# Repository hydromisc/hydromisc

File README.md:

# Hydromisc

This is a single PCBA with all the necessary I/O to automate a typical
small to mid-size hydroponic grow, controllable over Wi-Fi. It may also
be suitable for aquariums, ponds, or any other biological or chemical
process involving water treatment. Inputs and outputs include:

* 8x 12 V, 1 A outputs, intended for solenoid valves (but usable for other
actuators too)
* 6x 12 V, 0.5 A ouputs, intended for pumps, with current monitoring
* 4x 12 V, 0.25 A outputs, intended for peristaltic dosing pumps, with analog
voltage control
* 2x direct interfaces to a pH probe or other ion-selective electrode
* 2x direct interfaces to an EC (electrical conductivity) probe, reading around 1000 uS
* 2x direct interfaces to a resistive sensor (thermistor, photoresistor,
etc.), reading around 10k
* 2x digital interface to a temperature and humidity sensor
* 2x digital interface to a strain gauge (to measure weight or pressure)

Typical hydroponic practice is to maintain the solution at a target EC and
pH, using EC as a proxy for fertilizer concentration and dosing acid or
(rarely) alkali to adjust pH. I'm using this board now to control injector
pumps in a drain-to-waste system, open-loop with manual adjustment, and
also to maintain closed-loop EC and pH in a recirculating system.

## Firmware

The board is managed by an ESP32. Install the
[ESP-IDF](https://github.com/espressif/esp-idf) framework from Espressif,
and build and load the firmware from an ESP-IDF command prompt.

The board is a Wi-Fi client. The name and password for its access point
must be compiled in to the program, in Espressif's usual way, with `idf.py
menuconfig`. The board will automatically get an IP address over DHCP,
so you'll probably want to configure your router or other DHCP server to
assign a static IP based on the MAC address. The MAC address is unique
per board, since that's serialized in the ESP32 module.

The current firmware implements a simple interface to read the sensors
and write the actuators over http. I'm currently sequencing everything with
some shell scripts initiated by cron jobs on a Raspberry Pi, which invoke
curl to command this board. Any device and programming language capable of
making http requests could be used, though.

The outputs are described as "solenoid", "pump", and "dosing pump",
because that's the purpose for which I'm personally using them, and the
present interface is named around that model. They can of course be
used for other types of load too. The software interface is easily
extended if the present commands are inadequate or too confusingly-named.

    $ curl 'http://hydromisc/solenoid?k=3&t=20&'\
    'dosingA=90&dosingB=90&dosingPh=210&dosingAux=0'
    { "result": "solenoiding" }

Solenoid output k is energized for t seconds. For the same period,
the four dosing pumps are also energized, with the respective duty
cycles from 0 (off) to 254 (full on, ~12 VDC). The voltage applied to
the dosing pump is very roughly linear in duty cycle, but both that map
and the map from voltage to speed are quite inexact. If you're closing
the loop (e.g., dosing acid to achieve a particular pH), then this may
not matter, since your control loop will automatically correct that. If
accuracy is important, then the pump should be calibrated, for example
by measuring the amount of liquid dispensed using a graduated cylinder
or weighing scale.

The solenoid output is powered for three seconds after the pumps stop.
This is to avoid closing the solenoid valves with pressure in the system,
since the pumps will continue to operate briefly after losing power. If
the dosing pumps feed directly into a single reservoir, then this and
everything else about the solenoids may be ignored.

    $ curl 'http://hydromisc/pump?k=4&t=15'
    { "result": "pumping" }

Pump output k is energized for t seconds. The measured current (up to about
500 mA) is recorded.

    $ curl 'http://hydromisc/current'
    { "result": "current","current": [ 71, 65, 74, 69, 78, 74, 80, 73, 63,
    73, 65, 68, 74, 64, 60 ] }

The current from the most recent /pump is reported, in units of milliamps
at one sample per second. If this hasn't yet completed, a full-length
trace is reported but future samples are 0.

    $ curl 'http://hydromisc/stop'
    { "result": "stopping" }

All (solenoid, pump, dosing pump) outputs are de-energized immediately.

    $ curl 'http://hydromisc/sensors'
    { "result": "sensors", "ec0": 984, "ec1": 47, "ph0": 41, "ph1": -320,
    "dcr0": 210000, "dcr1": 210000, "temp0": 25.7, "humidity0": 54.0,
    "temp1": -9999.9, "humidity1": -9999.9, "sg0": 0, "sg1": -1 }

All sensors are measured and reported.

The pH electrode voltage is returned in millivolts, and your software
must convert to pH. To a first order, the map from voltage to pH is
linear, with zero volts corresponding to pH = 7.0, and a slope around
59 mV/unit around room temperature (which may be calculated using the
Nernst equation).

You should calibrate by measuring the voltage in two solutions of known
pH (e.g., 4.0 and 6.9), and interpolating linearly between the two. For
example:

    const V69 = 8;      // millivolts in pH 6.9 calibration buffer
    const V40 = -152;   // millivolts in pH 4.0 calibration buffer

    const slope = (V69 - V40)/(6.9 - 4.0);

    let ph = 6.9 + (resp.ph0 - V69)/slope;

Your software must also correct for temperature if desired; though in
typical hydroponic applications, the pH is close enough to neutral that
it doesn't matter too much. To a first order, the slope changes with
temperature but the offset does not, so the tempco is very small when the
output voltage is small.

Other ion-selective electrodes (e.g., for nitrate, potassium, etc.) should
also work with this interface circuit. Consult the electrode documentation
for the calibration procedure, which should be specified in terms of
millivolts from the meter. The reference electrode would need to go to
the BNC shell (Vref ~ 1.2 V), not ground.

EC is returned directly in microsiemens, uS. For example, a resistance
of 1kohm is equal to 1000 uS. Your software must convert based on the
cell dimensions (to convert from uS to uS/cm; a cell constant of 1 cm
is typical so that may be trivial), and also perform any temperature
compensation if desired. If you already have a different EC meter,
then you can use that with a sample of hydroponic solution to transfer
calibration. If not, then you can calibrate in a solution of 1000 mg/L
sodium chloride (table salt), which has conductivity of 2000 uS/cm at
25 degrees Celsius.

In concept, any two wires the right length and distance apart (e.g.,
on the order of 1 cm) could be immersed in solution, and could serve
as your EC electrode. You may prefer to buy a purpose-built electrode,
though. That may have a plastic sheath that protects the electrodes
from mechanical damage with a slit to avoid trapping air bubbles. The
electrode material should also have good electrochemical properties.
Inexpensive electrodes will generally use stainless steel. The most
expensive electrodes will use a thin coating of platinum black, which
reduces error by reducing the series resistance due to electrode
polarization. Either is likely fine in practice.

Electrodes may also be inserted into media, in which case they measure
a product of the solution EC and the media water content. An EC channel
can also be used as a binary liquid level sensor, by placing the
electrodes just below the threshold level. In such use, take care that
the electrodes are far enough apart that surface tension can't hold
a drop of solution even when they aren't immersed.

To measure water (or other) temperature, you can use a thermistor. Some
EC or pH probes will have a thermistor integrated in the probe,
or you can buy one separately. The resistance of that thermistor
(or any other resistive sensor) is returned directly in ohms. Your
software must convert to temperature. For a typical NTC thermistor,
the logarithm of the resistance is proportional to the reciprocal of
absolute temperature. For example:

    // we calibrated at 22 degrees Celsius, and measured 10435 ohms
    const calLogR = Math.log(10435);
    const calTemp = 22;

    // from some random NTC thermistor datasheet, or you could also do a
    // two-point calibration
    const slope = 0.0002578;

    let Tinv = 1/(273 + calTemp) + slope*(Math.log(resp.dcr0) - calLogR);
    let T = 1/Tinv - 273;

I'm also using that interface with a photoresistor to count hours of sun,
though I'm doing a simple binary threshold (to distinguish direct sun
vs. shade) and not a full continuous calibration.

To measure air temperature and humidity, connect an AM2301 on either 2x3
position connector to ground (black), +3V3 (red), and DIG_xOUT (yellow).
Temperature is returned in degrees Celsius, and humidity in percent RH.
A pull-up resistor from red to yellow may be required if the wires are long,
since we otherwise just get the ESP32's on-chip pull-up.

To measure a strain gauge, connect an HX710 to ground, +3V3, DIG_xCK
(SCK), and DIG_xIN (DOUT). The result is returned in raw ADC units,
which you can calibrate to force or pressure with a linear offset and
scale. I use this to measure liquid level with a "bubbler" system,
measuring the hydrostatic pressure in an air-filled tube at the bottom
of the tank. (It's necessary to bubble a slow trickle of air through the
tube, or else tiny leaks will cause it to eventually fill with water; but
since I'm already aerating my tanks, that just takes a tee and a needle
valve. Such systems are common in process industries, crude but cheap
and reliable. My system is okay but not great, since the pressure sensor
has a large tempco. I used an additional AM2301 very close to the sensor
to compensate, but there's still an inch or so worth of residual error.)

You can simultaneously connect an HX710 and an AM2301 to the same
2x3 connector, since they use different data pins.

    $ curl 'http://hydromisc/conf?dosingAPhase=63&dosingBPhase=4032&'\
    'dosingPhPhase=4095&dosingAuxPhase=4095&runBigPump=1'
    { "result": "configured" }

By default, the dosing pumps run continuously during a /solenoid call.
Here they can also be configured to run intermittently, in 100 ms
intervals on a 12-interval (1.2 s) period. The operation of each dosing
pump may be specified here as a bitmap, 12 bits as a decimal number. For
example, the decimal number 63 is equal to 12'b000000111111, so dosing
pump A is on with duty cycle 1/2, 600 ms on followed by 600 ms off. The
decimal number 4032 is equal to 12'b111111000000, so dosing pump B is
also on with duty cycle 1/2 but with opposite phase.

When peristaltic pumps are used as fertilizer injectors, this intermittent
operation can achieve lower injection rates than can be reliably achieved
with low pump voltage (since the transfer characteristic from voltage to
flow varies a lot at low voltage). The phase may be chosen to minimize
risk of mixing before dilution.

By default, the output BIG_PUMP is energized during a /solenoid call. This
may be disabled by setting runBigPump=0.

## Getting Hardware

For the moment, this hardware isn't commercially available in assembled
form. (That may change, since this is open hardware that anyone can build
and sell; I'll add links if and when it does.) You'll therefore have to
buy the bare PCB and parts kit, and assemble yourself. This PCBA has no
leadless or fine-pitch components, so it can be hand-assembled with a
soldering iron and moderate skill.

Note that rev A of the PCB has one major erratum, a missing pull-up on
ESP32_EN, plus some smaller issues that degrade analog performance. I've
corrected these in rev C, which is the head revision in git, but never
actually built and tested that. So it's possible there's still a mistake,
though the risk should be small. Full details of the changes are in
[board/README.md](https://github.com/hydromisc/hydromisc/blob/master/board/README.md).

Total cost to build one board is around:

Item | Cost
----------- | --------------
bare PCB, PCBWay | $30
components, Digi-Key | $60

All connectors are Molex Mini-Fit Jr., a very popular series. It's
possible to solder the cable-end connectors rather than crimping
them, but not recommended. The official crimp tool is expensive. I've used
a third-party "SN-28B", which isn't actually designed for that family
but is cheap and barely adequate, if I crimp first with the largest
die and then again with the middle one.

To program the board, use any USB-to-serial adapter with +3V3 logic levels,
for example an FT232R. Take care that you need access to RTS, which some
such boards and cables don't break out. On CN15, connect:

* ground to ground
* +3V3 to nothing
* USBSER_RX to ESP32_TXD0
* USBSER_TX to ESP32_RXD0
* USBSER_DTR to ESP32_IO0
* USBSER_RTS to ESP32_EN

Program with `idf.py flash` in the usual way. Disconnect digital expansion
devices when programming, since they can interfere.

For complete automated control of EC and pH, you might add:

Item | Cost
----------- | --------------
pH electrode, Yieryi | $15
EC electrode | $15
3x aquarium-type dosing pump | $30
water fill solenoid valve | $15

See my brief
[review of the sensors and actuators now cheaply available on Chinese markets](https://github.com/hydromisc/hydromisc/blob/master/doc/sensors-actuators.md).

Then you might periodically (e.g., minutes to hours) measure EC and pH
with /sensors. You could also monitor solution level, using another EC
electrode positioned high in the tank or using a float switch. The board
has no binary digital inputs, but the DC resistance or EC channels work
with switch contacts too. Then using /solenoid, you could add water,
fertilizer, and acid as required to maintain desired liquid level,
EC and pH.

You would typically aim to keep pH constant, for example with simple
hysteretic (bang-bang) control--add phosphoric if the pH is too high,
or add potassium carbonate if the pH is too low, with a significant
deadband (e.g., 0.5 units) so the acid and alkali don't fight it out
and leave too much potassium phosphate in the solution. In most cases
the alkali would actually be unnecessary, since the natural alkalinity
of the water supplies all necessary pH rise. That's the reason why only
one dosing pump channel is labeled "pH", though the AUX channel could
be used for alkali if desired.

Control of EC is more complicated, since unwanted ions (e.g., sodium
and chloride) will accumulate over time in the solution. So constant EC
probably means rising unwanted ions but falling NPK, and will eventually
result in deficiency. If you maintain constant EC, then you'll need to
change the reservoir often. You can waste less water by allowing slow
rise, though managing that without detailed water analyses is somewhat
uncertain. In all cases, fertilizer should be dosed in a way that doesn't
risk mixing of Part A and Part B before they're fully diluted, to avoid
precipitation (nutrient lockout) from the reaction between calcium ions
and phosphate or sulfate. For example, dose at opposite ends of the tank,
or allow sufficient time to mix between parts.

Of course more complicated automation is possible too. For example, this
board could manage multiple reservoirs simultaneously, or sense EC and
pH both in the reservoir and in returning solution from NFT channels, or
manage fertilizer injectors for a drain-to-waste system. The large number
of inputs and outputs is intended to provide flexibility to interface to
almost any conceivable system's sensors and actuators, with the automated
behavior determined by the software that commands this board.

## Circuit Explanation

Input power is +12 V, which feeds the power outputs directly. It also
feeds a buck converter that makes our +5V, and a buck converter that
makes Vuser, arbitrarily adjustable with a trimpot. An LDO makes +3V3
from +5V, and all our logic runs from that.

The ESP32 is a module with integrated antenna. It would be better for
the antenna tuning if the board outline had a cutout for that, but I
preferred mechanical robustness over antenna range. The ESP32 drives
two 8-bit serial-input, parallel-output shift registers, which function
as GPIO expanders and gate drivers for the pump and solenoid power
FETs. Max current for the solenoid outputs is determined by thermals due
to I^2\*Rdson. I haven't measured that temperature rise, but something
around an amp should be quite safe. Max current for the pump outputs is
determinated by the 2.2 ohm low-side current-sense resistor, and could
be increased by decreasing that.

The dosing pump gates are driven directly by ESP32 PWM outputs. A
series LC makes the negative-ground equivalent of a buck converter
on those outputs, enabling us to drive the dosing pumps not with PWM
but with a programmable DC voltage. This decreases radiated emissions,
and provides something like a constant voltage output as long as the
converter remains in continuous conduction.

The pump outputs return their ground current through a current-sense
resistor, and an ESP32 ADC channel measures the voltage across that. This
enables us to measure pump current. For example, if pump current
is much higher when pumping water than when pumping air, this lets us
measure the volume of water pumped out of a tray by measuring when the
pump current drops. The current can also be used for health monitoring, to
confirm the pump is actually connected and operating with expected load.

A pH electrode develops a voltage around 0 V at pH 7, plus or minus
roughly 59 mV per pH unit at room temperature. Its output impedance may be
many megohms, so we measure that voltage with an electrometer-type opamp,
with femtoamp input current. To mitigate leakage resistance across our
PCB (e.g., due to ionic contamination from flux residue), we surround
the sensitive trace with a driven shield held at the same voltage as that
sensitive node. I've seen no trouble due to leakage even without cleaning
flux, though I live in a dry climate and it would be better to clean that.

Since the pH electrode voltage may be positive or negative and we don't
have a negative supply, we connect its "ground" to a 1.2 V reference. This
means that any electrical connection between our circuit ground and
the solution being measured will result in an incorrect measurement,
though the shunt regulator that generates that rail can survive a short
to ground without damage. The shield of the BNC connectors is 1.2 V,
not ground. As long as the board is powered from an isolated power supply
(for example, a typical mains-operated power brick), no further attention
should be required; but take care not to de-isolate it, for example by
attaching board ground to any metal that touches the solution.

Even with DC isolation, a significant 60 Hz (or 50 Hz) component may
be present on the pH probe voltage. If this saturates the front-end
amplifier, then no subsequent low-pass could recover the correct DC
voltage. We address this with a capacitor across the pH probe. The
resulting low-pass time constant is poorly-controlled, since it's a
function of the probe output resistance.  That's fine in practice though,
since pH shouldn't change significantly over any timescale faster than
minutes.

We pull both sides of the EC electrode up to +3V3 through 1k
resistors, so they both rest at +3V3 with respect to circuit ground, 0 V
differential. To measure EC, we pull one side to ground through an n-FET,
and then measure the voltage of the other, making a voltage divider
between the known 1k and the unknown resistance under test. We then
repeat the process for the other side, restoring zero DC voltage across
the electrode to avoid polarization. The EC electrode is also AC-coupled
through 22 uF ceramic capacitors, guaranteeing zero DC voltage even if
the software misbehaves or the resistors don't perfectly match and, more
importantly, presenting high imepedance at DC so the EC electrode doesn't
short out a pH electrode immersed in the same sample cup. Assuming EC
around 2 mS/cm and cell constant around 1 cm, we get a high-pass time
constant around 4 ms, which is much slower than our measurement period
of ~500 us. Electrolytic capacitors can't be used for that AC-coupling,
since the leakage current is too high.

A similar approach may be used to measure EC with almost
any microcontroller and no additional components beyond the
reference resistors and AC-coupling capacitors, by configuring that
microcontroller's I/O pin as an output low to ground it. I chose to use
the external FETs here because I'd run out of microcontroller pins, and
because the lower and more consistent Rdson improves accuracy at high EC
(since that appears in series with the resistance under test).

## Information Security

None whatsoever. Use this only behind a firewall (like a typical
residential NAT router), on a network with trusted users only. If you
need remote access, expose it through a properly-secured jump box or VPN,
not directly.

## Warranty and Life Safety

THERE IS NO WARRANTY FOR THIS SOFTWARE OR HARDWARE, TO THE EXTENT
PERMITTED BY APPLICABLE LAW. WE PROVIDE THE SOFTWARE OR HARDWARE "AS IS"
WITHOUT WARRANTY OF ANY KIND, EITHER EXPRESSED OR IMPLIED, INCLUDING,
BUT NOT LIMITED TO, THE IMPLIED WARRANTIES OF MERCHANTABILITY AND FITNESS
FOR A PARTICULAR PURPOSE.

DO NOT USE THIS SOFTWARE OR HARDWARE IN SITUATIONS WHERE ITS FAILURE COULD
RESULT IN DANGER TO HUMAN LIFE. For example, don't dose concentrated acid
and rely on correct operation of this board to safely dilute it--instead
dose a higher volume of less concentrated acid, or use safer chemistry
(monopotassium phosphate, etc.). Also think carefully about the risk of
overflowing water, dead plants or fish, and other damage, and don't rely
on software to prevent it.

## License

The firmware is licensed under the GPLv3 or later. The legal framework
for open hardware is poorly-established, but you may build and sell, give
away, or otherwise transfer any number of hydromisc boards, provided that:

* any software loaded on the board is free software (as defined by
any OSI-approved license), and that software is not intended primarily
as a bootloader or other tool to load, program, or otherwise enable use
of non-free software; and

* you do not falsely claim ownership of the design, or any affiliation
with this project beyond your permission to build boards per above.

## Next steps

For now, this project is useful only to people with sufficient programming
skill to build and load the firmware, and to use the http interface
above. For future, it would be nice to:

* Integrate with existing control software (Mycodo, home automation packages,
etc.)

* And/or, add logic on the ESP32 itself for timed irrigations and
closed-loop dosing based on measured pH and EC, to allow this board
to work standalone with no need for the network except for initial
configuration. Firmware to log and graph (as a web page) sensors over
time would also be helpful in standalone use.

* Add a friendly mode to configure Wi-Fi settings, since those currently
must be compiled in. For example, if some combination of pins is jumpered
at startup, appear as a Wi-Fi access point to which the user can connect
and provide the real access point name and password. Then save those
credentials in flash, and use them after reset.

* Clean up how concurrency is managed in the firmware. The present code
seems to work, but it's a lazy hack that's hard to analyze for races.

I might eventually do some of that work myself, but I have limited time
and welcome other contributors. Please feel free to use GitHub issues to
discuss potential new features or anything else.

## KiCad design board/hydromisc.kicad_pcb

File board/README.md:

There are three revisions of the PCB:

* rev A - I built this, and it works except that I forgot the pull-up on
ESP32_EN. Solder a 10k resistor from ESP32_EN to +3V3 (for example, near
CN15), or else the ESP32 module won't start when the programmer is
disconnected.

* rev B - This adds the missing pull-up, as R54. It also adds R55 and
R56 from Vuser to ground, enabling use of LM2596 parts from vendors
(e.g. ON Semi) that have much higher leakage current than the National/TI
original, up to 2 mA! A lightly-loaded Vuser may lose regulation when
Ileakage\*Rpulldown > Vsetpoint, and that R was previously just the
feedback divider.

* rev C - This adds capacitors to create a passive low-pass on the pH
inputs, improving 60 Hz (or 50 Hz) rejection and thus reducing noise
e.g. when the probe is connected with long wires. It also changes the
series resistors between Vref and the BNC shield from 1k to zero-ohm,
since the shunt regulator that makes Vref can survive a short-circuit
to ground with no problem and that resistance worsens noise performance.

The head revision in git is rev C; but I've never actually built this
revision, so it's possible there's still a mistake. That risk should be
very small, though. I'll amend this note if/when someone builds rev C
and reports back.

This is a two-layer board, designed to PCBWay's standard design rules.
Almost any vendor should be able to make this, though. 1.6mm thick,
1 oz/ft^2 copper.

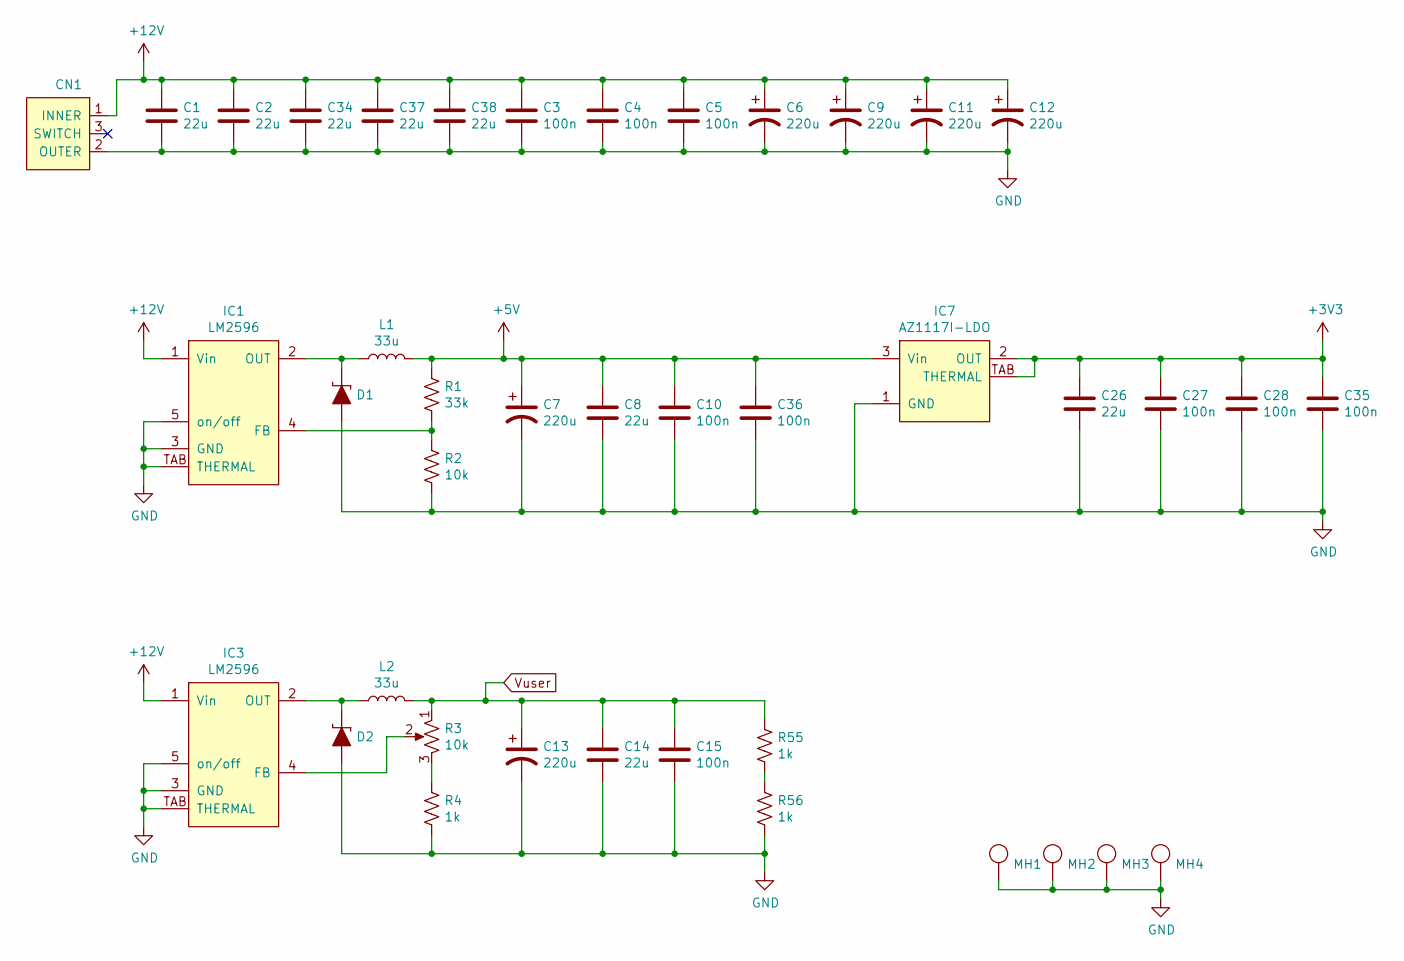
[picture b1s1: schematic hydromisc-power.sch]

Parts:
C1, C2, C8, C14, C26, C34, C37, C38: 22u; HM_1206
C3, C4, C5, C10, C15, C27, C28, C35, C36: 100n; HM_0603
C6, C7, C9, C11, C12, C13: 220u; HM_C_8MM_3.5MM
CN1: DC_COAX_POWER_NO_SHIELD; HM_DC_COAX_POWER_PJ-102AH
D1, D2: diode-schottky; HM_DIODE_SMB
IC1, IC3: LM2596; HM_TO-263-5
IC7: AZ1117I-LDO; HM_SOT-223
L1, L2: 33u; HM_L_SUMIDA_104CDMCCDS
MH1, MH2, MH3, MH4: MOUNTING_HOLE; HM_MOUNTING_HOLE_6MM_3MM
R1: 33k; HM_0603
R2: 10k; HM_0603
R3: 10k; HM_TRIMPOT_AB_HA06
R4, R55, R56: 1k; HM_0603

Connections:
+3V3: C26.1, C27.1, C28.1, C35.1, IC7.2 (OUT), IC7.TAB (THERMAL); also elsewhere on the board
+5V: C7.1, C8.1, C10.1, C36.1, IC7.3 (Vin), L1.2, R1.1; also elsewhere on the board
+12V: C1.1, C2.1, C3.1, C4.1, C5.1, C6.1, C9.1, C11.1, C12.1, C34.1, C37.1, C38.1, CN1.1 (INNER), IC1.1 (Vin), IC3.1 (Vin); also elsewhere on the board
GND: C1.2, C2.2, C3.2, C4.2, C5.2, C6.2, C7.2, C8.2, C9.2, C10.2, C11.2, C12.2, C13.2, C14.2, C15.2, C26.2, C27.2, C28.2, C34.2, C35.2, C36.2, C37.2, C38.2, CN1.2 (OUTER), D1.A, D2.A, IC1.3 (GND), IC1.5 (on/off), IC1.TAB (THERMAL), IC3.3 (GND), IC3.5 (on/off), IC3.TAB (THERMAL), IC7.1 (GND), MH1.1, MH2.1, MH3.1, MH4.1, R2.2, R4.2, R56.2; also elsewhere on the board
unnamed: D1.K, IC1.2 (OUT), L1.1
unnamed: D2.K, IC3.2 (OUT), L2.1
unnamed: IC1.4 (FB), R1.2, R2.1
unnamed: IC3.4 (FB), R3.2
unnamed: R3.3, R4.1
unnamed: R55.2, R56.1
Vuser: C13.1, C14.1, C15.1, L2.2, R3.1, R55.1; also elsewhere on the board

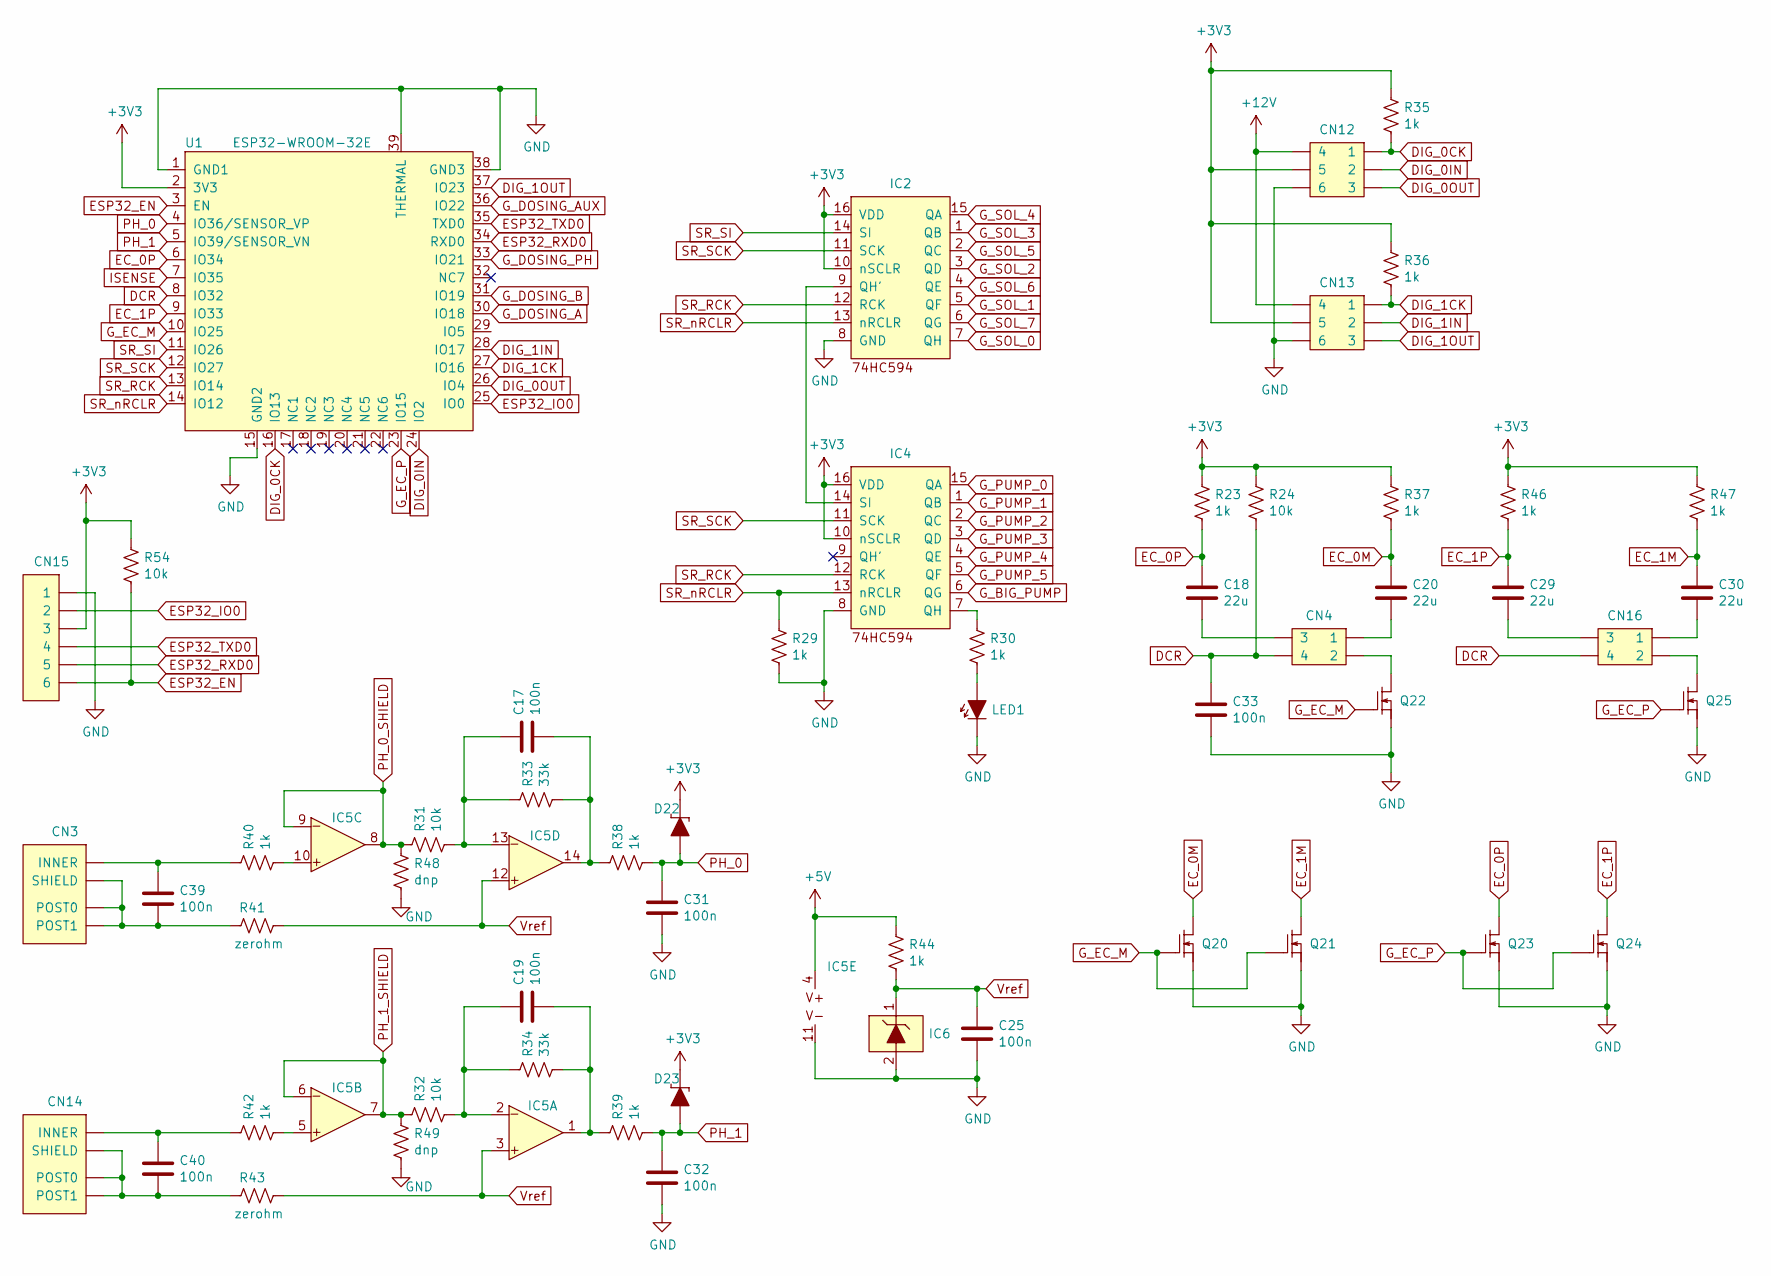
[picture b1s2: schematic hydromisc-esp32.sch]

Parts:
C17, C19, C25, C31, C32, C33, C39, C40: 100n; HM_0603
C18, C20, C29, C30: 22u; HM_1206
CN3, CN14: COAX_CONNECTOR; HM_BNC_MOLEX_TH_RA
CN4, CN16: MOLEX_2x2; HM_MOLEX_172448_2x2
CN12, CN13: MOLEX_2x3; HM_MOLEX_172448_2x3
CN15: HEADER_6; HM_HEADER_6_0.100_INCH
D22, D23: diode-schottky; HM_SOD-123
IC2, IC4: 74HC594; HM_SOIC-16
IC5: opamp; HM_SOIC-14
IC6: vref-diode; HM_SOT-23_123
LED1: diode-led; HM_LED_CUBE_3MM
Q20, Q21, Q22, Q23, Q24, Q25: NFET; HM_SOT-23_123
R23, R29, R30, R35, R36, R37, R38, R39, R40, R42, R44, R46, R47: 1k; HM_0603
R24, R31, R32, R54: 10k; HM_0603
R33, R34: 33k; HM_0603
R41, R43: zerohm; HM_0603
R48, R49: dnp; HM_0603
U1: ESP32-WROOM-32E; HM_ESP32-WROOM-32E

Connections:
+3V3: CN12.5, CN13.5, CN15.3, D22.K, D23.K, IC2.10 (nSCLR), IC2.16 (VDD), IC4.10 (nSCLR), IC4.16 (VDD), R23.1, R24.1, R35.2, R36.2, R37.1, R46.1, R47.1, R54.1, U1.2 (3V3); also elsewhere on the board
+5V: IC5.4 (V+), R44.1; also elsewhere on the board
+12V: CN12.4, CN13.4; also elsewhere on the board
DCR: C33.1, CN4.4, CN16.4, R24.2, U1.8 (IO32)
DIG_0CK: CN12.1, R35.1, U1.16 (IO13)
DIG_0IN: CN12.2, U1.24 (IO2)
DIG_0OUT: CN12.3, U1.26 (IO4)
DIG_1CK: CN13.1, R36.1, U1.27 (IO16)
DIG_1IN: CN13.2, U1.28 (IO17)
DIG_1OUT: CN13.3, U1.37 (IO23)
EC_0M: C20.1, Q20.3 (D), R37.2
EC_0P: C18.1, Q23.3 (D), R23.2, U1.6 (IO34)
EC_1M: C30.1, Q21.3 (D), R47.2
EC_1P: C29.1, Q24.3 (D), R46.2, U1.9 (IO33)
ESP32_EN: CN15.6, R54.2, U1.3 (EN)
ESP32_IO0: CN15.2, U1.25 (IO0)
ESP32_RXD0: CN15.5, U1.34 (RXD0)
ESP32_TXD0: CN15.4, U1.35 (TXD0)
GND: C25.2, C31.2, C32.2, C33.2, CN12.6, CN13.6, CN15.1, IC2.8 (GND), IC4.8 (GND), IC5.11 (V-), IC6.2 (-), LED1.K, Q20.2 (S), Q21.2 (S), Q22.2 (S), Q23.2 (S), Q24.2 (S), Q25.2 (S), R29.2, R48.2, R49.2, U1.1 (GND1), U1.15 (GND2), U1.38 (GND3), U1.39 (THERMAL); also elsewhere on the board
G_BIG_PUMP: IC4.6 (QG); also elsewhere on the board
G_DOSING_A: U1.30 (IO18); also elsewhere on the board
G_DOSING_AUX: U1.36 (IO22); also elsewhere on the board
G_DOSING_B: U1.31 (IO19); also elsewhere on the board
G_DOSING_PH: U1.33 (IO21); also elsewhere on the board
G_EC_M: Q20.1 (G), Q21.1 (G), Q22.1 (G), U1.10 (IO25)
G_EC_P: Q23.1 (G), Q24.1 (G), Q25.1 (G), U1.23 (IO15)
G_PUMP_0: IC4.15 (QA); also elsewhere on the board
G_PUMP_1: IC4.1 (QB); also elsewhere on the board
G_PUMP_2: IC4.2 (QC); also elsewhere on the board
G_PUMP_3: IC4.3 (QD); also elsewhere on the board
G_PUMP_4: IC4.4 (QE); also elsewhere on the board
G_PUMP_5: IC4.5 (QF); also elsewhere on the board
G_SOL_0: IC2.7 (QH); also elsewhere on the board
G_SOL_1: IC2.5 (QF); also elsewhere on the board
G_SOL_2: IC2.3 (QD); also elsewhere on the board
G_SOL_3: IC2.1 (QB); also elsewhere on the board
G_SOL_4: IC2.15 (QA); also elsewhere on the board
G_SOL_5: IC2.2 (QC); also elsewhere on the board
G_SOL_6: IC2.4 (QE); also elsewhere on the board
G_SOL_7: IC2.6 (QG); also elsewhere on the board
ISENSE: U1.7 (IO35); also elsewhere on the board
unnamed: C17.1, IC5.13 (D-), R31.2, R33.1
unnamed: C17.2, IC5.14 (DOUT), R33.2, R38.1
unnamed: C18.2, CN4.3
unnamed: C19.1, IC5.2 (A-), R32.2, R34.1
unnamed: C19.2, IC5.1 (AOUT), R34.2, R39.1
unnamed: C20.2, CN4.1
unnamed: C29.2, CN16.3
unnamed: C30.2, CN16.1
unnamed: C39.1, CN3.INNER, R40.1
unnamed: C39.2, CN3.POST0, CN3.POST1, CN3.SHIELD, R41.1
unnamed: C40.1, CN14.INNER, R42.1
unnamed: C40.2, CN14.POST0, CN14.POST1, CN14.SHIELD, R43.1
unnamed: CN4.2, Q22.3 (D)
unnamed: CN16.2, Q25.3 (D)
unnamed: IC2.9 (QH'), IC4.14 (SI)
unnamed: IC4.7 (QH), R30.1
unnamed: IC5.5 (B+), R42.2
unnamed: IC5.10 (C+), R40.2
unnamed: LED1.A, R30.2
PH_0: C31.1, D22.A, R38.2, U1.4 (IO36/SENSOR_VP)
PH_0_SHIELD: IC5.8 (COUT), IC5.9 (C-), R31.1, R48.1
PH_1: C32.1, D23.A, R39.2, U1.5 (IO39/SENSOR_VN)
PH_1_SHIELD: IC5.6 (B-), IC5.7 (BOUT), R32.1, R49.1
SR_RCK: IC2.12 (RCK), IC4.12 (RCK), U1.13 (IO14)
SR_SCK: IC2.11 (SCK), IC4.11 (SCK), U1.12 (IO27)
SR_SI: IC2.14 (SI), U1.11 (IO26)
SR_nRCLR: IC2.13 (nRCLR), IC4.13 (nRCLR), R29.1, U1.14 (IO12)
Vref: C25.1, IC5.3 (A+), IC5.12 (D+), IC6.1 (+), R41.2, R43.2, R44.2

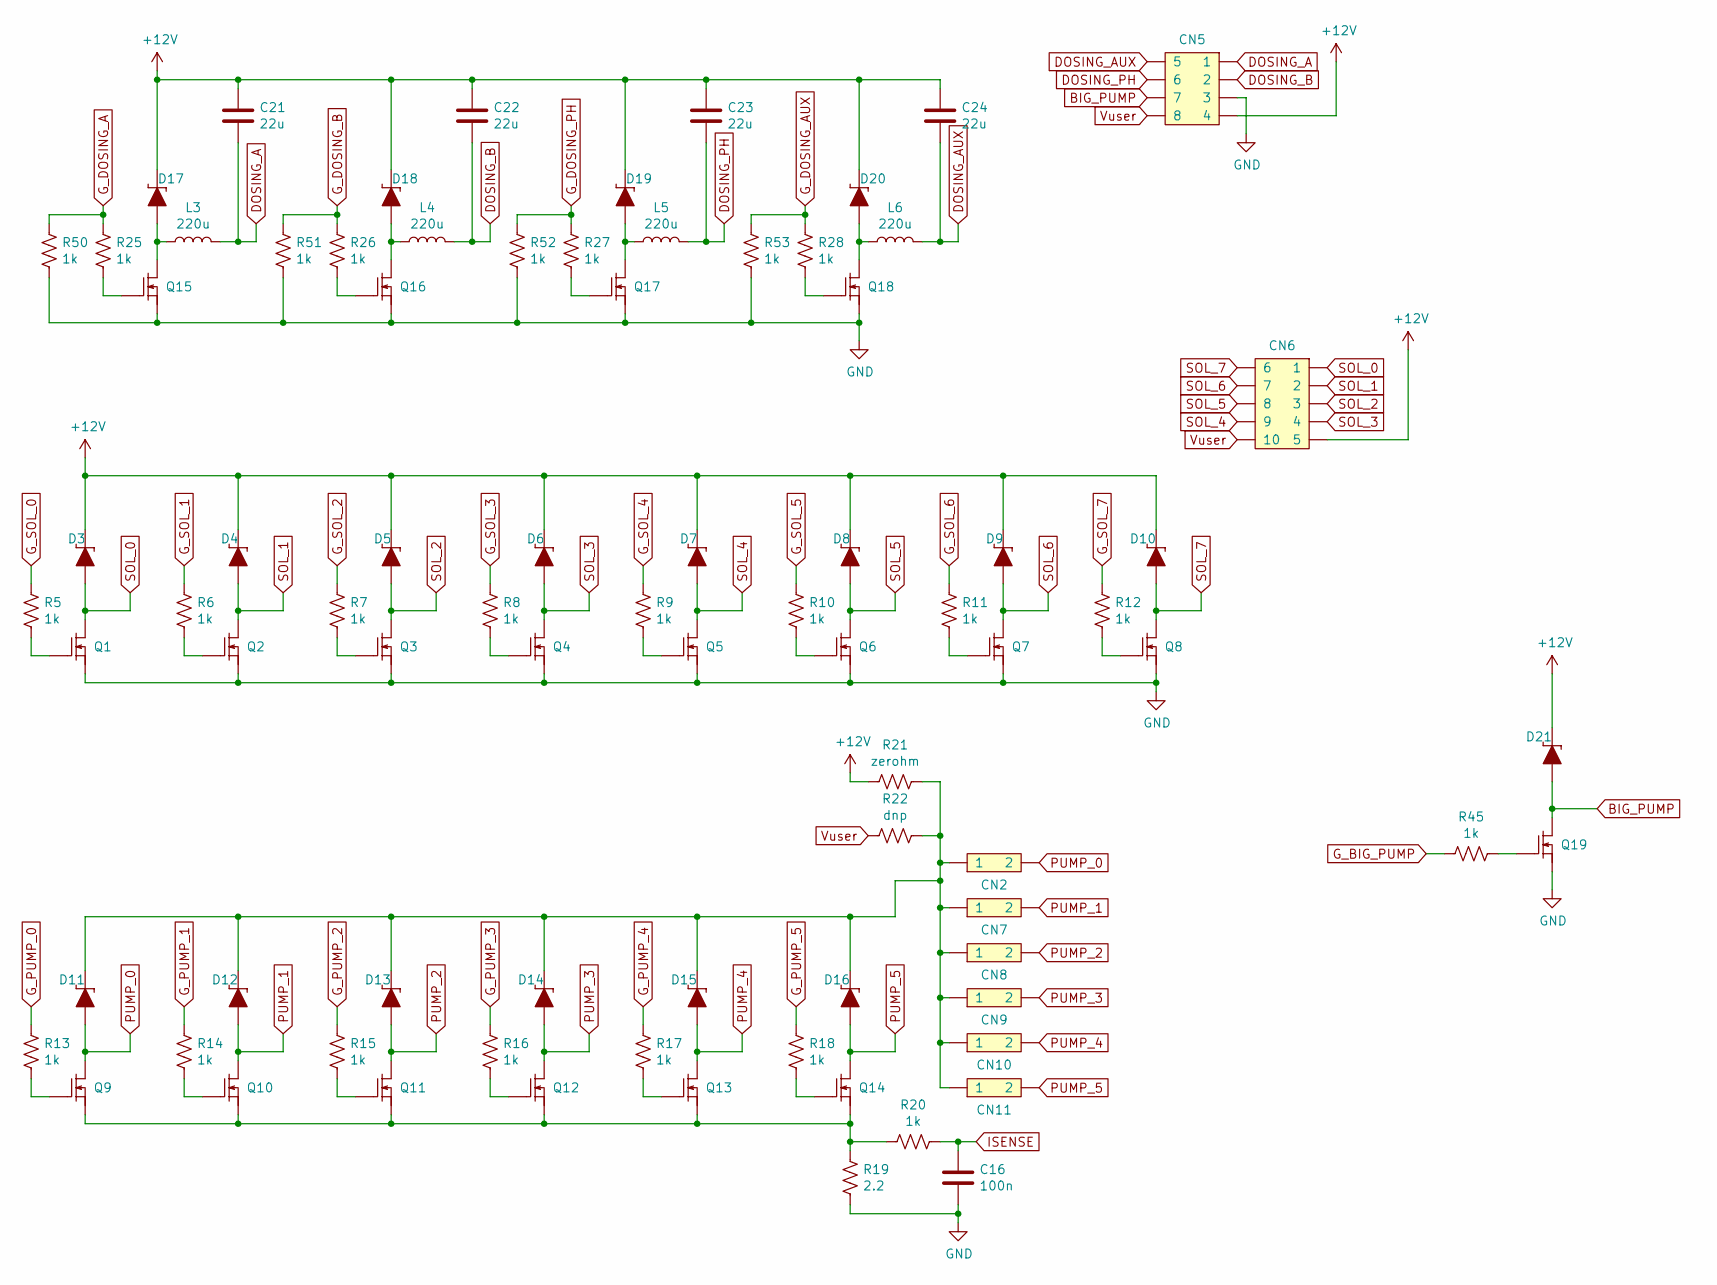
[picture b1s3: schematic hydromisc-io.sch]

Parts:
C16: 100n; HM_0603
C21, C22, C23, C24: 22u; HM_1206
CN2, CN7, CN8, CN9, CN10, CN11: MOLEX_2x1; HM_MOLEX_172448_2x1
CN5: MOLEX_2x4; HM_MOLEX_172448_2x4
CN6: MOLEX_2x5; HM_MOLEX_172448_2x5
D3, D4, D5, D6, D7, D8, D9, D10, D11, D12, D13, D14, D15, D16, D17, D18, D19, D20, D21: diode-schottky; HM_SOD-123
L3, L4, L5, L6: 220u; HM_L_MURATA_LQH44
Q1, Q2, Q3, Q4, Q5, Q6, Q7, Q8, Q9, Q10, Q11, Q12, Q13, Q14, Q15, Q16, Q17, Q18, Q19: NFET; HM_SOT-23_123
R5, R6, R7, R8, R9, R10, R11, R12, R13, R14, R15, R16, R17, R18, R20, R25, R26, R27, R28, R45, R50, R51, R52, R53: 1k; HM_0603
R19: 2.2; HM_2010
R21: zerohm; HM_1206
R22: dnp; HM_1206

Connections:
+12V: C21.1, C22.1, C23.1, C24.1, CN5.4, CN6.5, D3.K, D4.K, D5.K, D6.K, D7.K, D8.K, D9.K, D10.K, D17.K, D18.K, D19.K, D20.K, D21.K, R21.2; also elsewhere on the board
BIG_PUMP: CN5.7, D21.A, Q19.3 (D)
DOSING_A: C21.2, CN5.1, L3.2
DOSING_AUX: C24.2, CN5.5, L6.2
DOSING_B: C22.2, CN5.2, L4.2
DOSING_PH: C23.2, CN5.6, L5.2
GND: C16.2, CN5.3, Q1.2 (S), Q2.2 (S), Q3.2 (S), Q4.2 (S), Q5.2 (S), Q6.2 (S), Q7.2 (S), Q8.2 (S), Q15.2 (S), Q16.2 (S), Q17.2 (S), Q18.2 (S), Q19.2 (S), R19.1, R50.2, R51.2, R52.2, R53.2; also elsewhere on the board
G_BIG_PUMP: R45.2; also elsewhere on the board
G_DOSING_A: R25.1, R50.1; also elsewhere on the board
G_DOSING_AUX: R28.1, R53.1; also elsewhere on the board
G_DOSING_B: R26.1, R51.1; also elsewhere on the board
G_DOSING_PH: R27.1, R52.1; also elsewhere on the board
G_PUMP_0: R13.1; also elsewhere on the board
G_PUMP_1: R14.1; also elsewhere on the board
G_PUMP_2: R15.1; also elsewhere on the board
G_PUMP_3: R16.1; also elsewhere on the board
G_PUMP_4: R17.1; also elsewhere on the board
G_PUMP_5: R18.1; also elsewhere on the board
G_SOL_0: R5.1; also elsewhere on the board
G_SOL_1: R6.1; also elsewhere on the board
G_SOL_2: R7.1; also elsewhere on the board
G_SOL_3: R8.1; also elsewhere on the board
G_SOL_4: R9.1; also elsewhere on the board
G_SOL_5: R10.1; also elsewhere on the board
G_SOL_6: R11.1; also elsewhere on the board
G_SOL_7: R12.1; also elsewhere on the board
ISENSE: C16.1, R20.1; also elsewhere on the board
unnamed: CN2.1, CN7.1, CN8.1, CN9.1, CN10.1, CN11.1, D11.K, D12.K, D13.K, D14.K, D15.K, D16.K, R21.1, R22.1
unnamed: D17.A, L3.1, Q15.3 (D)
unnamed: D18.A, L4.1, Q16.3 (D)
unnamed: D19.A, L5.1, Q17.3 (D)
unnamed: D20.A, L6.1, Q18.3 (D)
unnamed: Q1.1 (G), R5.2
unnamed: Q2.1 (G), R6.2
unnamed: Q3.1 (G), R7.2
unnamed: Q4.1 (G), R8.2
unnamed: Q5.1 (G), R9.2
unnamed: Q6.1 (G), R10.2
unnamed: Q7.1 (G), R11.2
unnamed: Q8.1 (G), R12.2
unnamed: Q9.1 (G), R13.2
unnamed: Q10.1 (G), R14.2
unnamed: Q9.2 (S), Q10.2 (S), Q11.2 (S), Q12.2 (S), Q13.2 (S), Q14.2 (S), R19.2, R20.2
unnamed: Q11.1 (G), R15.2
unnamed: Q12.1 (G), R16.2
unnamed: Q13.1 (G), R17.2
unnamed: Q14.1 (G), R18.2
unnamed: Q15.1 (G), R25.2
unnamed: Q16.1 (G), R26.2
unnamed: Q17.1 (G), R27.2
unnamed: Q18.1 (G), R28.2
unnamed: Q19.1 (G), R45.1
PUMP_0: CN2.2, D11.A, Q9.3 (D)
PUMP_1: CN7.2, D12.A, Q10.3 (D)
PUMP_2: CN8.2, D13.A, Q11.3 (D)
PUMP_3: CN9.2, D14.A, Q12.3 (D)
PUMP_4: CN10.2, D15.A, Q13.3 (D)
PUMP_5: CN11.2, D16.A, Q14.3 (D)
SOL_0: CN6.1, D3.A, Q1.3 (D)
SOL_1: CN6.2, D4.A, Q2.3 (D)
SOL_2: CN6.3, D5.A, Q3.3 (D)
SOL_3: CN6.4, D6.A, Q4.3 (D)
SOL_4: CN6.9, D7.A, Q5.3 (D)
SOL_5: CN6.8, D8.A, Q6.3 (D)
SOL_6: CN6.7, D9.A, Q7.3 (D)
SOL_7: CN6.6, D10.A, Q8.3 (D)
Vuser: CN5.8, CN6.10, R22.2; also elsewhere on the board

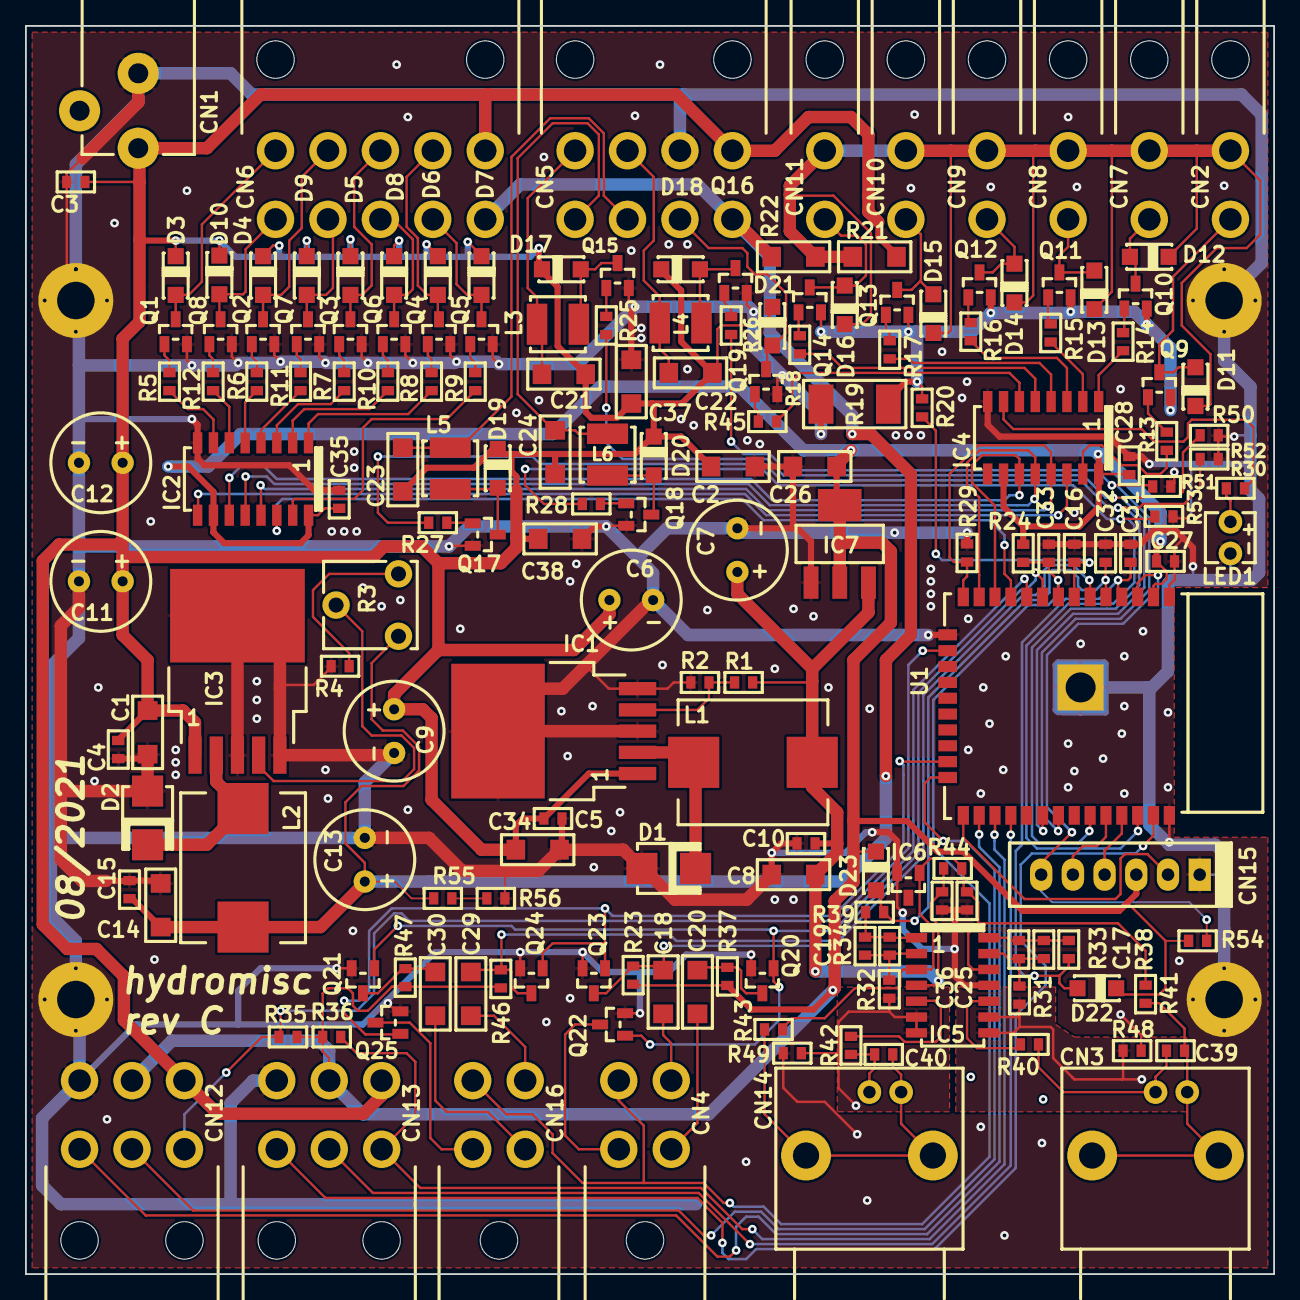
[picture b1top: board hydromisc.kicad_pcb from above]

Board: 2 copper layers, 100.0 x 100.0 mm, 179 parts (0 on the bottom side), 120 nets.

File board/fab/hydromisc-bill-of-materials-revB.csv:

"hydromisc bill of materials, rev B, Jul 2021",,,,
,,,,
Qty,Reference Designators,Value,Description,Digi-Key P/N
16,"C1, C2, C8, C14, C18, C20, C21, C22, C23, C24, C26, C29, C30, C34, C37, C38, ",22u,"capacitor, 1206, MLCC, 16 V, X5R",1276-2728-1-ND
16,"C3, C4, C5, C10, C15, C16, C17, C19, C25, C27, C28, C31, C32, C33, C35, C36, ",100n,"capacitor, 0603, MLCC, 25 V, X7R",1276-1006-1-ND
6,"C6, C7, C9, C11, C12, C13, ",220u,"capacitor, electrolytic, 25 V, through-hole radial",399-6112-ND
1,"CN1, ",,"connector, DC power, coaxial, 2.1 mm",CP-102AH-ND
6,"CN2, CN7, CN8, CN9, CN10, CN11, ",,"connector, Mini-Fit Jr., 2x1",WM16206-ND
2,"CN3, CN14, ",,"connector, BNC, right angle",WM5514-ND
2,"CN4, CN16, ",,"connector, Mini-Fit Jr., 2x2",WM16295-ND
1,"CN5, ",,"connector, Mini-Fit Jr., 2x4",WM17269-ND
1,"CN6, ",,"connector, Mini-Fit Jr., 2x5",WM17284-ND
2,"CN12, CN13, ",,"connector, Mini-Fit Jr., 2x3",WM17089-ND
1,"CN15, ",,"header, 0.100"", 6 position",S1022EC-06-ND
2,"D1, D2, ",,"diode, schottky, SMB",641-SS34B-HFCT-ND
21,"D3, D4, D5, D6, D7, D8, D9, D10, D11, D12, D13, D14, D15, D16, D17, D18, D19, D20, D21, D22, D23, ",,"diode, schottky, SOD-123",1655-1929-1-ND
2,"IC1, IC3, ",,"LM2596, buck controller with integrated switch, adjustable",LM2596DSADJR4GOSCT-ND
2,"IC2, IC4, ",,"74HC594, octal serial in parallel out shift register",74HC594DCT-ND
1,"IC5, ",,"LMC6024, opamp with ultra-low input current",296-35434-1-ND
1,"IC6, ",,"voltage reference, 1.2 V",576-2571-1-ND
1,"IC7, ",,"AZ1117I, low dropout linear regulator, 3.3 V",AZ1117IH-3.3TRG1DICT-ND
2,"L1, L2, ",33u,"inductor, 4.1 A",308-2500-1-ND
4,"L3, L4, L5, L6, ",220u,"inductor, 280 mA",490-LQH44PH221MPRLCT-ND
1,"LED1, ",,"LED, yellow",1497-1052-ND
25,"Q1, Q2, Q3, Q4, Q5, Q6, Q7, Q8, Q9, Q10, Q11, Q12, Q13, Q14, Q15, Q16, Q17, Q18, Q19, Q20, Q21, Q22, Q23, Q24, Q25, ",,"n-FET, SOT-23",DMG2302UK-7DICT-ND
3,"R1, R33, R34, ",33k,"resistor, 0603, 1%",CR0603-FX-3302ELFCT-ND
5,"R2, R24, R31, R32, R54, ",10k,"resistor, 0603, 1%",CR0603-FX-1002ELFCT-ND
1,"R3, ",10k,"trimpot, through-hole",478-601030-ND
42,"R4, R5, R6, R7, R8, R9, R10, R11, R12, R13, R14, R15, R16, R17, R18, R20, R23, R25, R26, R27, R28, R29, R30, R35, R36, R37, R38, R39, R40, R41, R42, R43, R44, R45, R46, R47, R50, R51, R52, R53, R55, R56, ",1k,"resistor, 0603, 1%",CR0603-FX-1001ELFCT-ND
1,"R19, ",2.2,"resistor, 2010, 5%",RMCF2010JT2R20CT-ND
1,"R21, ",zerohm,"resistor, 1206, zero-ohm",311-0.0ERTR-ND 
1,"R22, ",,do not populate,
2,"R48, R49, ",,do not populate,
1,"U1, ",,"ESP32 module with integrated antenna, 16 MB",1965-ESP32-WROOM-32E(16MB)CT-ND

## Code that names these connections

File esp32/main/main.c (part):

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#define ADC_DCR_SENSE                   ADC_CHANNEL_4

#define GPIO_EC_M_GATE                  25
#define GPIO_SR_SI                      26
#define GPIO_SR_SCK                     27
#define GPIO_SR_RCK                     14
#define GPIO_SR_nRCLR                   12

#define GPIO_DIG_0_CK                   13
#define GPIO_EC_P_GATE                  15
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    io_conf.mode = GPIO_MODE_OUTPUT;
    io_conf.pin_bit_mask = 
        (1ULL << GPIO_EC_M_GATE) |
        (1ULL << GPIO_SR_SI) |
        (1ULL << GPIO_SR_SCK) |
        (1ULL << GPIO_SR_RCK) |
        (1ULL << GPIO_SR_nRCLR) |
        (1ULL << GPIO_DIG_0_CK) |
        (1ULL << GPIO_EC_P_GATE) |
        (1ULL << GPIO_DIG_0_OUT) |
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    gpio_set_pull_mode(GPIO_DIG_1_OUT, GPIO_PULLUP_ONLY);
    gpio_set_level(GPIO_DIG_1_OUT, 1);

    gpio_set_level(GPIO_SR_SI, 0);
    gpio_set_level(GPIO_SR_SCK, 0);
    gpio_set_level(GPIO_SR_RCK, 0);
    gpio_set_level(GPIO_SR_nRCLR, 0);

    adc1_config_width(ADC_WIDTH_BIT_12);
    adc1_config_channel_atten(ADC_CURRENT_SENSE, ADC_ATTEN_DB_0);
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    portDISABLE_INTERRUPTS();
    int i;
    for(i = 15; i >= 0; i--) {
        gpio_set_level(GPIO_SR_SI, (sr_bits & (1 << i)) ? 1 : 0);
        ets_delay_us(1);
        gpio_set_level(GPIO_SR_SCK, 1);
        ets_delay_us(1);
        gpio_set_level(GPIO_SR_SCK, 0);
        ets_delay_us(1);
    }

    gpio_set_level(GPIO_SR_RCK, 1);
    ets_delay_us(1);
    gpio_set_level(GPIO_SR_RCK, 0);
    ets_delay_us(1);
    gpio_set_level(GPIO_SR_nRCLR, 1);
    portENABLE_INTERRUPTS();
}

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
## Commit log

2021-07-02 Add labeled images of connectors.
2021-07-02 Add ESP32 firmware.
2021-07-02 Add .gitignore for ESP32 build artifacts.
2021-07-02 Add rev A schematics and layouts.
    This is tested and working, except that it's missing a pull-up on
    ESP32_EN. I'll correct this in rev B, or a 10k resistor could be
    hand-soldered from ESP32_EN to +3V3 (e.g., near CN15).
2021-07-02 Oops, need to add our custom symbol library.
2021-07-02 Add README.md, documenting both hardware and firmware.
2021-07-02 Update PCB to rev B.
    Add the missing pull-up on ESP32_EN, some pull-down on Vuser to
    fight off-brand LM2596 leakage current, and a README.md explaining.
2021-07-03 Add Gerbers, BOM, and PDF schematics for rev B.
    Also fix README.md, since current spec for dosing pumps was too high,
    limited by inductor.
2021-07-04 Oops, fix use of slope in pH calibration example.
    Also fix missing word, and improve introduction.
2021-07-04 Fix double word.
2021-07-08 Add kitspace.yaml
2021-08-15 Add capacitors directly across pH probes.
    This fixes a problem with 60 Hz (or 50 Hz) pickup, when the wires are
    long or the noise is coupling to the water. Also replace the 1k resistors
    to the shield with zero-ohm resistors, to further reduce that noise.
    This updates the board to rev C. Also check in PDF schematics, BOM,
    and Gerbers.
2021-08-25 Add images of sensors and actuators.
2021-08-25 Add review of sensors and actuators.
2021-10-17 Add a nutrient calculator.
2021-10-17 Fix incorrect Cu for S.T.E.M.
    The datasheet that I was using seems to have a typo. Also add
    ammonium sulfate, and tweak help text.
2021-10-17 Fix incorrect total N for Cornell lettuce formula.
2021-11-11 Fix minor typo
2021-11-13 Improve nutrient calculator help text.
2021-11-14 Add images for custom nutrient profile.
2021-11-14 Add article about custom nutrient blend.
2021-11-14 Fix typos, and expand slightly.
2021-11-14 Minor edits to custom nutrient article.
2021-11-14 Minor edit.
2021-11-15 Added SMD tag to SMD components for centroid data output.
2022-01-03 Acidify with phosphoric acid, not citric.

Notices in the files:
esp32/main/main.c:
Copyright 2021 Hydromisc contributors.
This program is free software: you can redistribute it and/or modify
it under the terms of the GNU General Public License as published by
the Free Software Foundation, either version 3 of the License, or
(at your option) any later version.
README.md:
License:
The firmware is licensed under the GPLv3 or later. The legal framework
for open hardware is poorly-established, but you may build and sell, give
away, or otherwise transfer any number of hydromisc boards, provided that: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
